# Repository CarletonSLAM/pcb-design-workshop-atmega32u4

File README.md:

## Example EAGLE projects that use ATmega32U4

- https://github.com/sparkfun/Pro_Micro
- https://github.com/adafruit/Atmega32u4-Breakout-Board

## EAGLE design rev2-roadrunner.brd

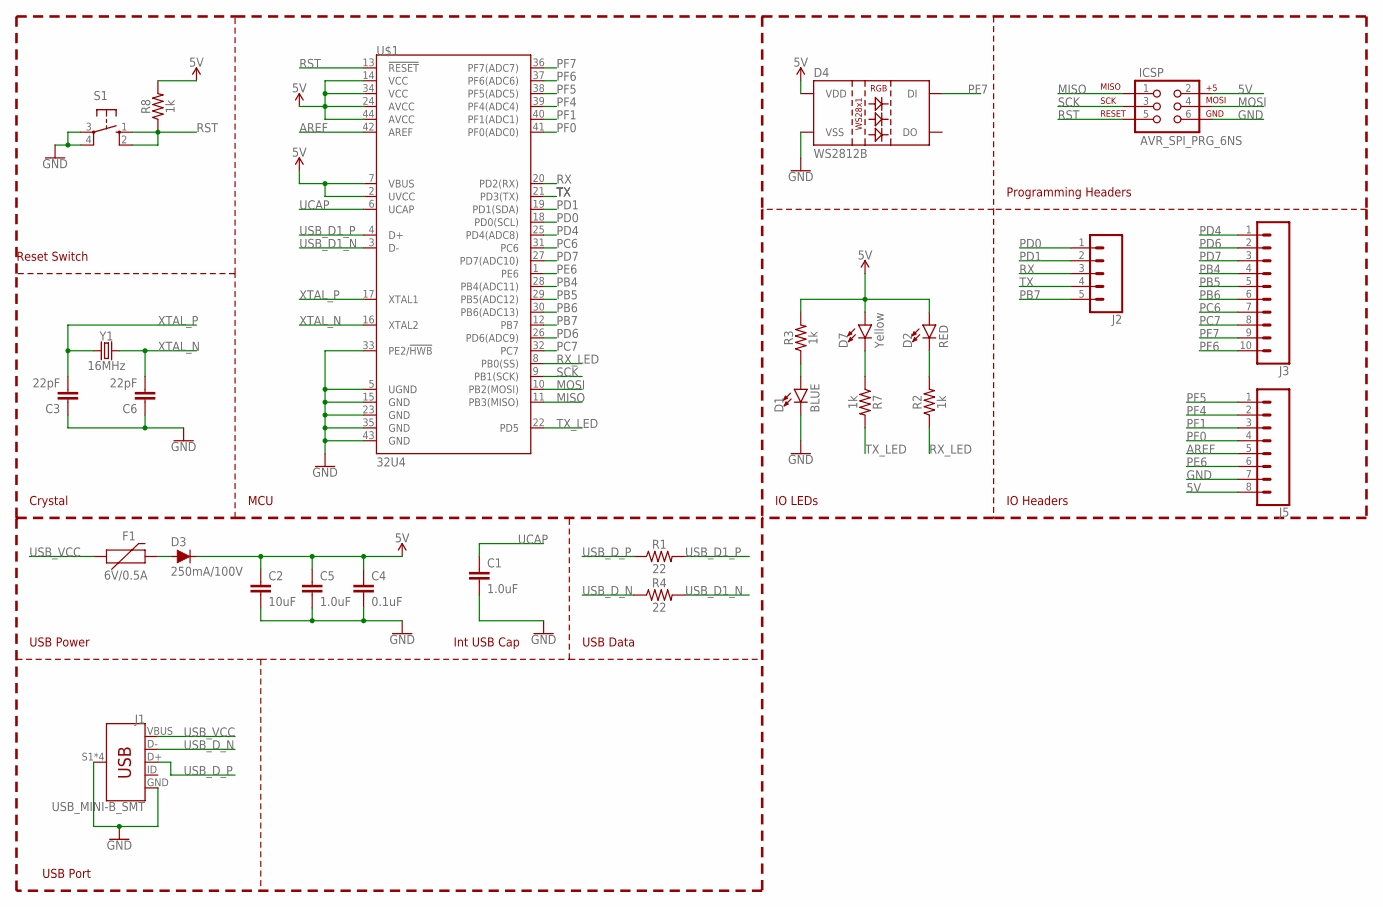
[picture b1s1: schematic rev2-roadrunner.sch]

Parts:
C1, C5: 1.0uF; 1206
C2: 10uF; 1206
C3, C6: 22pF; 1206
C4: 0.1uF; 1206
D1: BLUE; LED-1206
D2: RED; LED-1206
D3: 250mA/100V; SOD-323
D4: WS2812B
D7: Yellow; LED-1206
F1: 6V/0.5A; 1206
ICSP: AVR_SPI_PRG_6NS; 2X3-NS
J1: USB_MINI-B_SMT; USB-MINIB
J2: CONN_05; 1X05
J3: CONN_10"; 1X10
J5: CONN_08"; 1X08
R1, R4: 22; 1206
R2, R3, R7, R8: 1k; 1206
S1: 10-XX; B3F-10XX
U$1: 32U4; TQFP44
Y1: 16MHz; HC49US

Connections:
5V: C2.1, C4.1, C5.1, D2.A, D3.C, D4.1 (VDD), D7.A, ICSP.2, J5.8, R3.2, R8.2, U$1.2 (UVCC), U$1.7 (VBUS), U$1.14 (VCC), U$1.24 (AVCC), U$1.34 (VCC), U$1.44 (AVCC)
AREF: J5.5, U$1.42 (AREF)
GND: C1.2, C2.2, C3.1, C4.2, C5.2, C6.1, D1.C, D4.3 (VSS), ICSP.6, J1.GND, J1.S1 (SHIELD), J1.S2 (SHIELD), J1.S3 (SHIELD), J1.S4 (SHIELD), J5.7, S1.3, S1.4 (P1), U$1.5 (UGND), U$1.15 (GND), U$1.23 (GND), U$1.33 (PE2/!HWB), U$1.35 (GND), U$1.43 (GND)
MISO: ICSP.1, U$1.11 (PB3(MISO))
MOSI: ICSP.4, U$1.10 (PB2(MOSI))
unnamed: D1.A, R3.1
unnamed: D7.C, R7.1
unnamed: D2.C, R2.2
unnamed: D3.A, F1.2
PB4: J3.4, U$1.28 (PB4(ADC11))
PB5: J3.5, U$1.29 (PB5(ADC12))
PB6: J3.6, U$1.30 (PB6(ADC13))
PB7: J2.5, U$1.12 (PB7)
PC6: J3.7, U$1.31 (PC6)
PC7: J3.8, U$1.32 (PC7)
PD0: J2.1, U$1.18 (PD0(SCL))
PD1: J2.2, U$1.19 (PD1(SDA))
PD4: J3.1, U$1.25 (PD4(ADC8))
PD6: J3.2, U$1.26 (PD6(ADC9))
PD7: J3.3, U$1.27 (PD7(ADC10))
PE6: J5.6, U$1.1 (PE6)
PF0: J5.4, U$1.41 (PF0(ADC0))
PF1: J5.3, U$1.40 (PF1(ADC1))
PF4: J5.2, U$1.39 (PF4(ADC4))
PF5: J5.1, U$1.38 (PF5(ADC5))
PF6: J3.10, U$1.37 (PF6(ADC6))
PF7: D4.4 (DI), J3.9, U$1.36 (PF7(ADC7))
RST: ICSP.5, R8.1, S1.1 (S), S1.2 (S1), U$1.13 (!RESET)
RX: J2.3, U$1.20 (PD2(RX))
RX_LED: R2.1, U$1.8 (PB0(SS))
SCK: ICSP.3, U$1.9 (PB1(SCK))
TX: J2.4, U$1.21 (PD3(TX))
TX_LED: R7.2, U$1.22 (PD5)
UCAP: C1.1, U$1.6 (UCAP)
USB_D1_N: R4.2, U$1.3 (D-)
USB_D1_P: R1.2, U$1.4 (D+)
USB_D_N: J1.D-, R4.1
USB_D_P: J1.D+, R1.1
USB_VCC: F1.1, J1.VBUS
XTAL_N: C6.2, U$1.16 (XTAL2), Y1.2
XTAL_P: C3.2, U$1.17 (XTAL1), Y1.1

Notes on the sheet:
Programming Headers
IO Headers
MCU
IO LEDs
USB Port
Reset Switch
Crystal
USB Data
USB Power
Int USB Cap

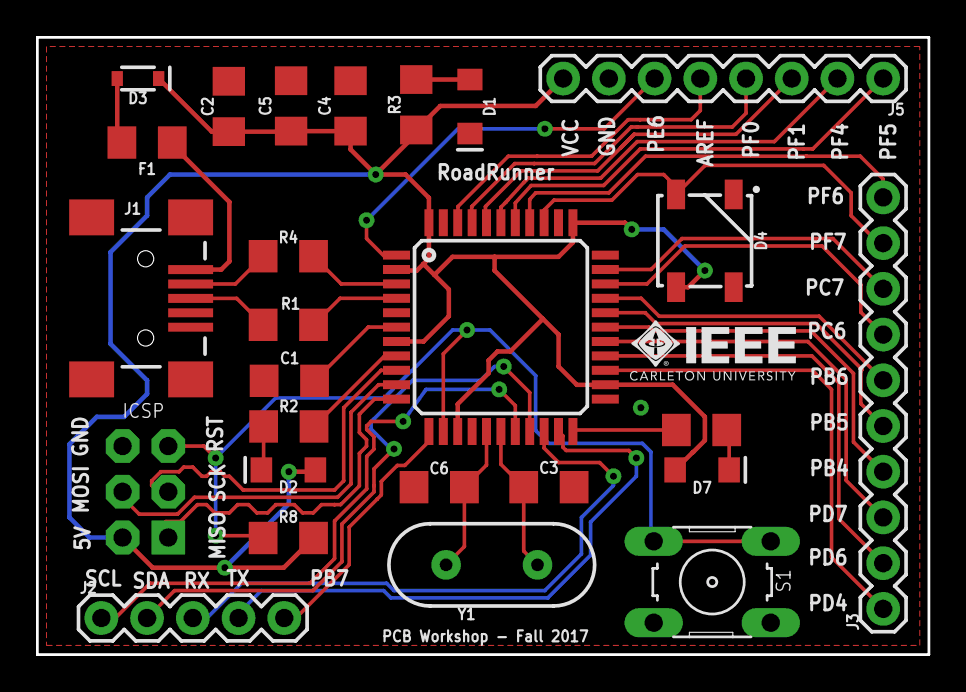
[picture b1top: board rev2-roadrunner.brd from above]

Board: 2 copper layers, 49.5 x 34.3 mm, 27 parts (0 on the bottom side), 41 nets.

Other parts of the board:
U$2: IEEECARLETON-ROADRUNNER

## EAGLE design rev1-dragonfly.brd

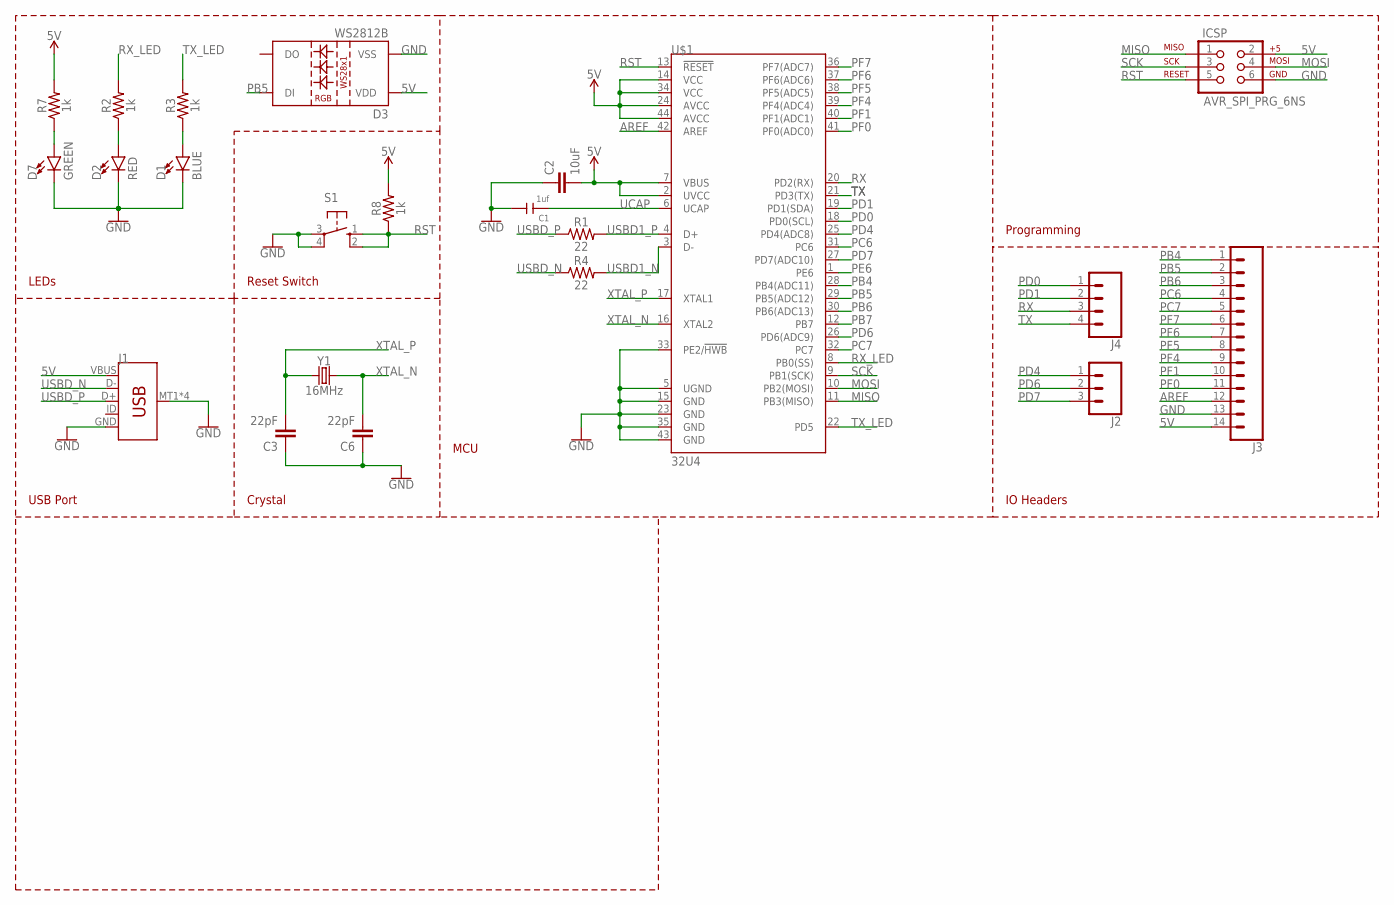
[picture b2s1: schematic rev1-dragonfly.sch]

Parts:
C1: 1uf; C0603
C2: 10uF; 0805
C3, C6: 22pF; 0603
D1: BLUE; LED-0603
D2: RED; LED-0603
D3: WS2812B
D7: GREEN; LED-0603
ICSP: AVR_SPI_PRG_6NS; 2X3-NS
J1: USB_MICRO-B_SMT; USB-MICROB
J2: CONN_03; 1X03
J3: CONN_14; 1X14
J4: CONN_04; 1X04
R1, R4: 22; 0603
R2, R3, R7, R8: 1k; 0805
S1: 10-XX; B3F-10XX
U$1: 32U4; TQFP44
Y1: 16MHz; HC49US

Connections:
5V: C2.2, D3.1 (VDD), ICSP.2, J1.VBUS, J3.14, R7.2, R8.2, U$1.2 (UVCC), U$1.7 (VBUS), U$1.14 (VCC), U$1.24 (AVCC), U$1.34 (VCC), U$1.44 (AVCC)
AREF: J3.12, U$1.42 (AREF)
GND: C1.2, C2.1, C3.1, C6.1, D1.C, D2.C, D3.3 (VSS), D7.C, ICSP.6, J1.GND, J1.MT1 (SHIELD), J1.MT2 (SHIELD), J1.P$1 (SHIELD), J1.P$2 (SHIELD), J3.13, S1.3, S1.4 (P1), U$1.5 (UGND), U$1.15 (GND), U$1.23 (GND), U$1.33 (PE2/!HWB), U$1.35 (GND), U$1.43 (GND)
MISO: ICSP.1, U$1.11 (PB3(MISO))
MOSI: ICSP.4, U$1.10 (PB2(MOSI))
unnamed: D1.A, R3.1
unnamed: D2.A, R2.1
unnamed: D7.A, R7.1
PB4: J3.1, U$1.28 (PB4(ADC11))
PB5: D3.4 (DI), J3.2, U$1.29 (PB5(ADC12))
PB6: J3.3, U$1.30 (PB6(ADC13))
PB7: U$1.12 (PB7)
PC6: J3.4, U$1.31 (PC6)
PC7: J3.5, U$1.32 (PC7)
PD0: J4.1, U$1.18 (PD0(SCL))
PD1: J4.2, U$1.19 (PD1(SDA))
PD4: J2.1, U$1.25 (PD4(ADC8))
PD6: J2.2, U$1.26 (PD6(ADC9))
PD7: J2.3, U$1.27 (PD7(ADC10))
PE6: U$1.1 (PE6)
PF0: J3.11, U$1.41 (PF0(ADC0))
PF1: J3.10, U$1.40 (PF1(ADC1))
PF4: J3.9, U$1.39 (PF4(ADC4))
PF5: J3.8, U$1.38 (PF5(ADC5))
PF6: J3.7, U$1.37 (PF6(ADC6))
PF7: J3.6, U$1.36 (PF7(ADC7))
RST: ICSP.5, R8.1, S1.1 (S), S1.2 (S1), U$1.13 (!RESET)
RX: J4.3, U$1.20 (PD2(RX))
RX_LED: R2.2, U$1.8 (PB0(SS))
SCK: ICSP.3, U$1.9 (PB1(SCK))
TX: J4.4, U$1.21 (PD3(TX))
TX_LED: R3.2, U$1.22 (PD5)
UCAP: C1.1, U$1.6 (UCAP)
USBD1_N: R4.2, U$1.3 (D-)
USBD1_P: R1.2, U$1.4 (D+)
USBD_N: J1.D-, R4.1
USBD_P: J1.D+, R1.1
XTAL_N: C6.2, U$1.16 (XTAL2), Y1.2
XTAL_P: C3.2, U$1.17 (XTAL1), Y1.1

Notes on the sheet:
Programming
IO Headers
MCU
LEDs
USB Port
Reset Switch
Crystal

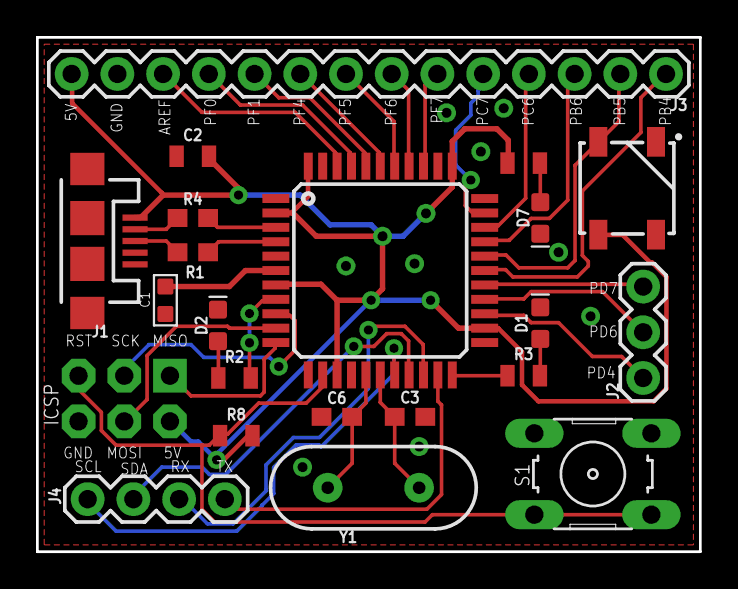
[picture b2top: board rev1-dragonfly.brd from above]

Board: 2 copper layers, 36.8 x 28.6 mm, 22 parts (0 on the bottom side), 37 nets.

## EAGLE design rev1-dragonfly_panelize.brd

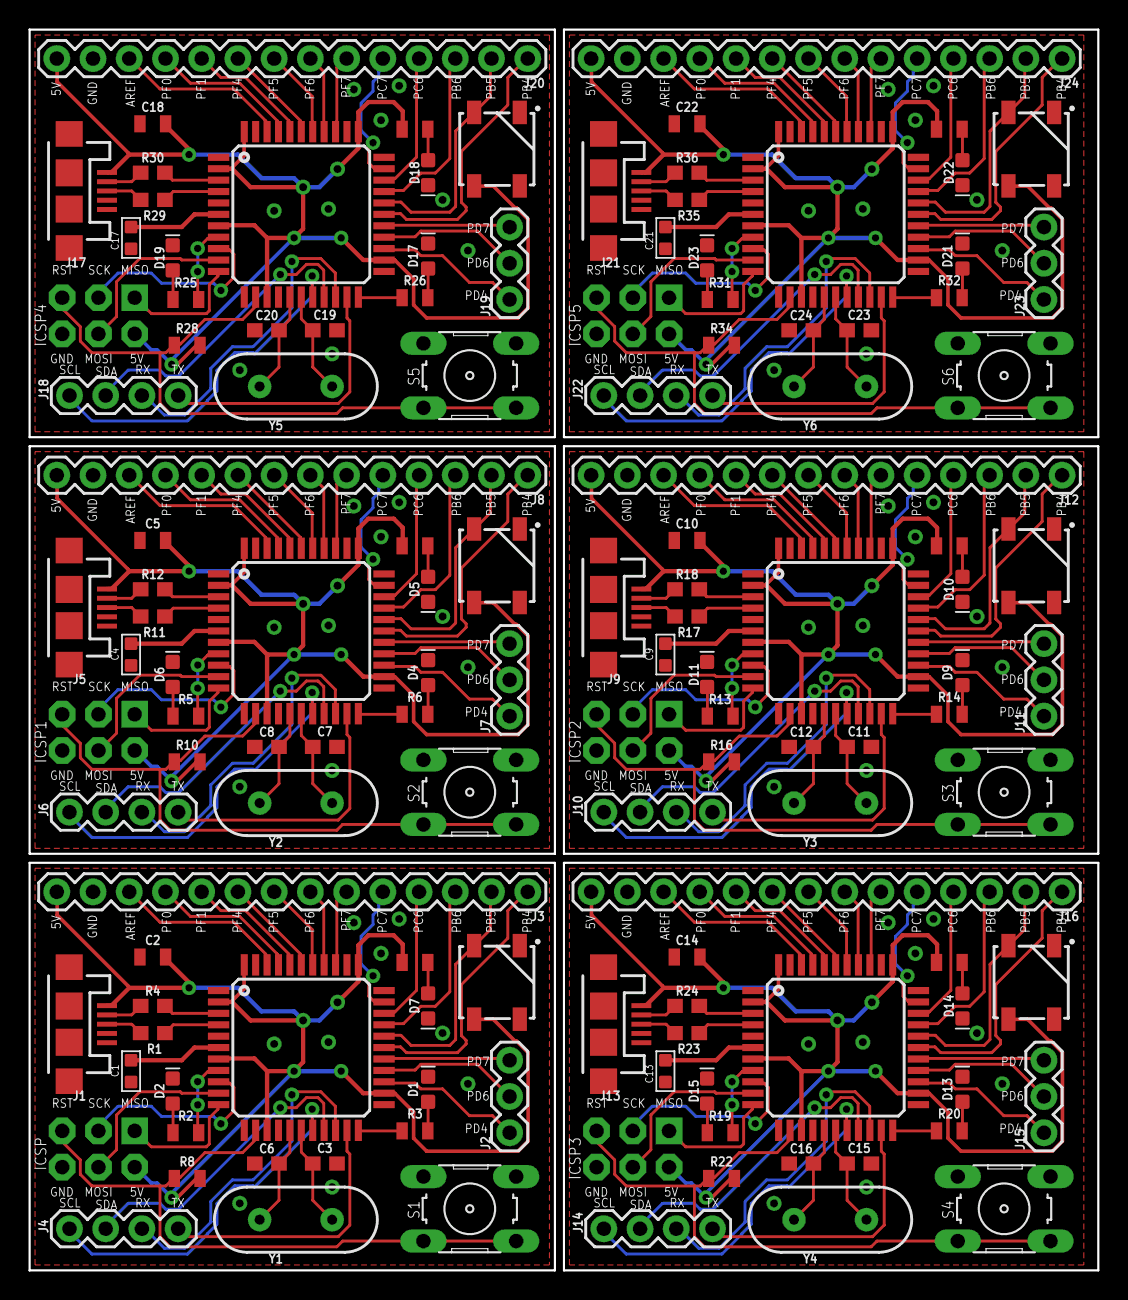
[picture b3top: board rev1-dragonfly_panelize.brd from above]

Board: 2 copper layers, 74.9 x 87.0 mm, 132 parts (0 on the bottom side), 222 nets.

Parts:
C1, C4, C9, C13, C17, C21: 1uf; C0603
C2, C5, C10, C14, C18, C22: 10uF; 0805
C3, C6, C7, C8, C11, C12, C15, C16, C19, C20, C23, C24: 22pF; 0603
D1, D4, D9, D13, D17, D21: BLUE; LED-0603
D2, D6, D11, D15, D19, D23: RED; LED-0603
D3, D8, D12, D16, D20, D24: WS2812B
D5, D7, D10, D14, D18, D22: GREEN; LED-0603
ICSP, ICSP1, ICSP2, ICSP3, ICSP4, ICSP5: AVR_SPI_PRG_6NS; 2X3-NS
J1, J5, J9, J13, J17, J21: USB-MICROB
J2, J7, J11, J15, J19, J23: 1X03
J3, J8, J12, J16, J20, J24: 1X14
J4, J6, J10, J14, J18, J22: 1X04
R1, R4, R11, R12, R17, R18, R23, R24, R29, R30, R35, R36: 22; 0603
R2, R3, R5, R6, R7, R8, R9, R10, R13, R14, R15, R16, R19, R20, R21, R22, R25, R26, R27, R28, R31, R32, R33, R34: 1k; 0805
S1, S2, S3, S4, S5, S6: B3F-10XX
U$1, U$2, U$3, U$4, U$5, U$6: 32U4; TQFP44
Y1, Y2, Y3, Y4, Y5, Y6: 16MHz; HC49US

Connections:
5V: C2.2, D3.1, ICSP.2, J1.VBUS, J3.14, R7.2, R8.2, U$1.2, U$1.7, U$1.14, U$1.24, U$1.34, U$1.44
5V1: C5.2, D8.1, ICSP1.2, J5.VBUS, J8.14, R9.2, R10.2, U$2.2, U$2.7, U$2.14, U$2.24, U$2.34, U$2.44
5V2: C10.2, D12.1, ICSP2.2, J9.VBUS, J12.14, R15.2, R16.2, U$3.2, U$3.7, U$3.14, U$3.24, U$3.34, U$3.44
5V3: C14.2, D16.1, ICSP3.2, J13.VBUS, J16.14, R21.2, R22.2, U$4.2, U$4.7, U$4.14, U$4.24, U$4.34, U$4.44
5V4: C18.2, D20.1, ICSP4.2, J17.VBUS, J20.14, R27.2, R28.2, U$5.2, U$5.7, U$5.14, U$5.24, U$5.34, U$5.44
5V5: C22.2, D24.1, ICSP5.2, J21.VBUS, J24.14, R33.2, R34.2, U$6.2, U$6.7, U$6.14, U$6.24, U$6.34, U$6.44
AREF: J3.12, U$1.42
AREF1: J8.12, U$2.42
AREF2: J12.12, U$3.42
AREF3: J16.12, U$4.42
AREF4: J20.12, U$5.42
AREF5: J24.12, U$6.42
GND: C1.2, C2.1, C3.1, C6.1, D1.C, D2.C, D3.3, D7.C, ICSP.6, J1.GND, J1.MT1, J1.MT2, J1.P$1, J1.P$2, J3.13, S1.3, S1.4, U$1.5, U$1.15, U$1.23, U$1.33, U$1.35, U$1.43
GND1: C4.2, C5.1, C7.1, C8.1, D4.C, D5.C, D6.C, D8.3, ICSP1.6, J5.GND, J5.MT1, J5.MT2, J5.P$1, J5.P$2, J8.13, S2.3, S2.4, U$2.5, U$2.15, U$2.23, U$2.33, U$2.35, U$2.43
GND2: C9.2, C10.1, C11.1, C12.1, D9.C, D10.C, D11.C, D12.3, ICSP2.6, J9.GND, J9.MT1, J9.MT2, J9.P$1, J9.P$2, J12.13, S3.3, S3.4, U$3.5, U$3.15, U$3.23, U$3.33, U$3.35, U$3.43
GND3: C13.2, C14.1, C15.1, C16.1, D13.C, D14.C, D15.C, D16.3, ICSP3.6, J13.GND, J13.MT1, J13.MT2, J13.P$1, J13.P$2, J16.13, S4.3, S4.4, U$4.5, U$4.15, U$4.23, U$4.33, U$4.35, U$4.43
GND4: C17.2, C18.1, C19.1, C20.1, D17.C, D18.C, D19.C, D20.3, ICSP4.6, J17.GND, J17.MT1, J17.MT2, J17.P$1, J17.P$2, J20.13, S5.3, S5.4, U$5.5, U$5.15, U$5.23, U$5.33, U$5.35, U$5.43
GND5: C21.2, C22.1, C23.1, C24.1, D21.C, D22.C, D23.C, D24.3, ICSP5.6, J21.GND, J21.MT1, J21.MT2, J21.P$1, J21.P$2, J24.13, S6.3, S6.4, U$6.5, U$6.15, U$6.23, U$6.33, U$6.35, U$6.43
MISO: ICSP.1, U$1.11
MISO1: ICSP1.1, U$2.11
MISO2: ICSP2.1, U$3.11
MISO3: ICSP3.1, U$4.11
MISO4: ICSP4.1, U$5.11
MISO5: ICSP5.1, U$6.11
MOSI: ICSP.4, U$1.10
MOSI1: ICSP1.4, U$2.10
MOSI2: ICSP2.4, U$3.10
MOSI3: ICSP3.4, U$4.10
MOSI4: ICSP4.4, U$5.10
MOSI5: ICSP5.4, U$6.10
unnamed: D1.A, R3.1
unnamed: D2.A, R2.1
unnamed: D7.A, R7.1
unnamed: D5.A, R9.1
unnamed: D4.A, R6.1
unnamed: D6.A, R5.1
unnamed: D10.A, R15.1
unnamed: D9.A, R14.1
unnamed: D11.A, R13.1
unnamed: D14.A, R21.1
unnamed: D13.A, R20.1
unnamed: D15.A, R19.1
unnamed: D18.A, R27.1
unnamed: D17.A, R26.1
unnamed: D19.A, R25.1
unnamed: D22.A, R33.1
unnamed: D21.A, R32.1
unnamed: D23.A, R31.1
PB1: D8.4, J8.2, U$2.29
PB2: J8.1, U$2.28
PB3: J8.3, U$2.30
PB4: J3.1, U$1.28
PB5: D3.4, J3.2, U$1.29
PB6: J3.3, U$1.30
PB9: D12.4, J12.2, U$3.29
PB10: J12.1, U$3.28
PB11: J12.3, U$3.30
PB13: D16.4, J16.2, U$4.29
PB14: J16.1, U$4.28
PB15: J16.3, U$4.30
PB17: D20.4, J20.2, U$5.29
PB18: J20.1, U$5.28
PB19: J20.3, U$5.30
PB21: D24.4, J24.2, U$6.29
PB22: J24.1, U$6.28
PB23: J24.3, U$6.30
PC1: J8.5, U$2.32
PC2: J8.4, U$2.31
PC3: J12.5, U$3.32
PC4: J12.4, U$3.31
PC5: J16.5, U$4.32
PC6: J3.4, U$1.31
PC7: J3.5, U$1.32
PC8: J16.4, U$4.31
PC9: J20.5, U$5.32
PC10: J20.4, U$5.31
PC11: J24.5, U$6.32
PC12: J24.4, U$6.31
PD0: J4.1, U$1.18
PD1: J4.2, U$1.19
PD2: J7.1, U$2.25
PD3: J7.2, U$2.26
PD4: J2.1, U$1.25
PD5: J7.3, U$2.27
PD6: J2.2, U$1.26
PD7: J2.3, U$1.27
PD8: J6.2, U$2.19
PD9: J6.1, U$2.18
PD10: J11.1, U$3.25
PD11: J11.2, U$3.26
PD12: J11.3, U$3.27
PD13: J10.2, U$3.19
PD14: J10.1, U$3.18
PD15: J15.1, U$4.25
PD16: J15.2, U$4.26
PD17: J15.3, U$4.27
PD18: J14.2, U$4.19
PD19: J14.1, U$4.18
PD20: J19.1, U$5.25
PD21: J19.2, U$5.26
PD22: J19.3, U$5.27
PD23: J18.2, U$5.19
PD24: J18.1, U$5.18
PD25: J23.1, U$6.25
PD26: J23.2, U$6.26
PD27: J23.3, U$6.27
PD28: J22.2, U$6.19
PD29: J22.1, U$6.18
PF0: J3.11, U$1.41
PF1: J3.10, U$1.40
PF2: J8.6, U$2.36
PF3: J8.7, U$2.37
PF4: J3.9, U$1.39
PF5: J3.8, U$1.38
PF6: J3.7, U$1.37
PF7: J3.6, U$1.36
PF8: J8.8, U$2.38
PF9: J8.9, U$2.39
PF10: J8.10, U$2.40
PF11: J8.11, U$2.41
PF12: J12.6, U$3.36
PF13: J12.7, U$3.37
PF14: J12.8, U$3.38
PF15: J12.9, U$3.39
PF16: J12.10, U$3.40
PF17: J12.11, U$3.41
PF18: J16.6, U$4.36
PF19: J16.7, U$4.37
PF20: J16.8, U$4.38
PF21: J16.9, U$4.39
PF22: J16.10, U$4.40
PF23: J16.11, U$4.41
PF24: J20.6, U$5.36
PF25: J20.7, U$5.37
PF26: J20.8, U$5.38
PF27: J20.9, U$5.39
PF28: J20.10, U$5.40
PF29: J20.11, U$5.41
PF30: J24.6, U$6.36
PF31: J24.7, U$6.37
PF32: J24.8, U$6.38
PF33: J24.9, U$6.39
PF34: J24.10, U$6.40
PF35: J24.11, U$6.41
RST: ICSP.5, R8.1, S1.1, S1.2, U$1.13
RST1: ICSP1.5, R10.1, S2.1, S2.2, U$2.13
RST2: ICSP2.5, R16.1, S3.1, S3.2, U$3.13
RST3: ICSP3.5, R22.1, S4.1, S4.2, U$4.13
RST4: ICSP4.5, R28.1, S5.1, S5.2, U$5.13
RST5: ICSP5.5, R34.1, S6.1, S6.2, U$6.13
RX: J4.3, U$1.20
RX1: J6.3, U$2.20
RX2: J10.3, U$3.20
RX3: J14.3, U$4.20
RX4: J18.3, U$5.20
RX5: J22.3, U$6.20
RX_LED: R2.2, U$1.8
RX_LED1: R5.2, U$2.8
RX_LED2: R13.2, U$3.8
RX_LED3: R19.2, U$4.8
RX_LED4: R25.2, U$5.8
RX_LED5: R31.2, U$6.8
SCK: ICSP.3, U$1.9
SCK1: ICSP1.3, U$2.9
SCK2: ICSP2.3, U$3.9
SCK3: ICSP3.3, U$4.9
SCK4: ICSP4.3, U$5.9
SCK5: ICSP5.3, U$6.9
TX: J4.4, U$1.21
TX1: J6.4, U$2.21
TX2: J10.4, U$3.21
TX3: J14.4, U$4.21
TX4: J18.4, U$5.21
TX5: J22.4, U$6.21
TX_LED: R3.2, U$1.22
TX_LED1: R6.2, U$2.22
TX_LED2: R14.2, U$3.22
TX_LED3: R20.2, U$4.22
TX_LED4: R26.2, U$5.22
TX_LED5: R32.2, U$6.22
UCAP: C1.1, U$1.6
UCAP1: C4.1, U$2.6
UCAP2: C9.1, U$3.6
UCAP3: C13.1, U$4.6
UCAP4: C17.1, U$5.6
UCAP5: C21.1, U$6.6
USBD1_N: R4.2, U$1.3
USBD1_N1: R12.2, U$2.3
USBD1_N2: R18.2, U$3.3
USBD1_N3: R24.2, U$4.3
USBD1_N4: R30.2, U$5.3
USBD1_N5: R36.2, U$6.3
USBD1_P: R1.2, U$1.4
USBD1_P1: R11.2, U$2.4
USBD1_P2: R17.2, U$3.4
USBD1_P3: R23.2, U$4.4
USBD1_P4: R29.2, U$5.4
USBD1_P5: R35.2, U$6.4
USBD_N: J1.D-, R4.1
USBD_N1: J5.D-, R12.1
USBD_N2: J9.D-, R18.1
USBD_N3: J13.D-, R24.1
USBD_N4: J17.D-, R30.1
USBD_N5: J21.D-, R36.1
USBD_P: J1.D+, R1.1
USBD_P1: J5.D+, R11.1
USBD_P2: J9.D+, R17.1
USBD_P3: J13.D+, R23.1
USBD_P4: J17.D+, R29.1
USBD_P5: J21.D+, R35.1
XTAL_N: C6.2, U$1.16, Y1.2
XTAL_N1: C8.2, U$2.16, Y2.2
XTAL_N2: C12.2, U$3.16, Y3.2
XTAL_N3: C16.2, U$4.16, Y4.2
XTAL_N4: C20.2, U$5.16, Y5.2
XTAL_N5: C24.2, U$6.16, Y6.2
XTAL_P: C3.2, U$1.17, Y1.1
XTAL_P1: C7.2, U$2.17, Y2.1
XTAL_P2: C11.2, U$3.17, Y3.1
XTAL_P3: C15.2, U$4.17, Y4.1
XTAL_P4: C19.2, U$5.17, Y5.1
XTAL_P5: C23.2, U$6.17, Y6.1

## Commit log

2017-08-12 Added Rev1
2017-08-12 adde Rev2
2017-08-12 Added proper eagle files
2017-08-12 Finalized Board and Schematic design
2017-08-12 Before Autorouter
2017-08-12 Fixed Routes after Autorouter
2017-08-12 Added attributes for crystal
2017-08-13 Re-routed by hand + Moved C1 down
2017-08-14 Added Icons and redid routing
2017-11-05 Added arduino and avr demos
2017-11-05 Removed hex files
2017-11-05 deleted other hex file

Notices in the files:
parts and their libraries:
SparkFun-Capacitors: Licensing: Creative Commons ShareAlike 4.0 International - https://creativecommons.org/licenses/by-sa/4.0
